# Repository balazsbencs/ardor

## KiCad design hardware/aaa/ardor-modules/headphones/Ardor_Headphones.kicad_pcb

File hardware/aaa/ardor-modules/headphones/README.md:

# Ardor Optional stereo headphones — M1

An external stereo line-level source feeds the local TPA6132A2 and charge pump. No mixer or external negative supply is required.

Power from an external regulated **5 V / 50 mA** supply budget. These figures reserve operating margin; they are not measured consumption. No onboard input regulator or reverse-power protection is provided. Use only the named rails and connect host GND. Budget each fitted module separately.

[Single-page schematic](review/schematic.pdf) · [Component placement](review/pcb-assembly.svg) · [Front routing](review/pcb-front.svg) · [Back routing and connector legends](review/pcb-back.svg)

## Connector pins

All connectors/jumpers are 2.54 mm headers. **Square pad = pin 1.** Pin numbers below are native schematic/PCB numbers, not left-to-right screen positions. Back-side text is read from the back of the physical board. The same reference names appear on multiple modules; use this board’s table. **J101 pin assignments differ between module types; harnesses are not interchangeable.**

| Connector | Pin | Signal |
|---|---|---|
| J102 | 1 | AUDIO_L |
| J102 | 2 | GND |
| J102 | 3 | AUDIO_R |
| J101 | 1 | +5V |
| J101 | 2 | GND |
| J101 | 3 | HP_ENABLE |
| J602 | 1 | HP_L |
| J602 | 2 | HP_R |
| J602 | 3 | GND |

## Wiring and commissioning

Connect an external stereo line-level DAC/codec to J102: pin 1 left, pin 2 ground, pin 3 right; each **≤1 Vrms**. J602 goes to a TRS headphone socket: pin 1 tip/left, pin 2 ring/right, pin 3 sleeve/GND. The sleeve/bushing bonds the enclosure through the local CHASSIS/GND link. Use headphones of **32 Ω or greater**; there is no balanced output.

J101 pin 3 **HP_ENABLE** is a 3.3 V logic input. LOW or disconnected disables the amplifier; HIGH enables it. Keep it low until audio and 5 V are stable, then start at low volume and ramp up. Do not drive enable above the amplifier’s supply plus 0.3 V when unpowered. Both gain pins are grounded, selecting **−6 dB inverting gain**. A 1 Vrms input gives about 0.47 Vrms / 6.8 mW per channel into 32 Ω after the 2.2 Ω output resistors (nominal calculation, not a measured result).

The TPA6132A2 charge-pump flying/storage capacitors, exposed-pad ground and input DC blocking are all local. HPVDD/HPVSS are internal rails and must not be connected to external power. This module deliberately carries the optional QFN amplifier and its added assembly/X-ray cost so other features do not pay for it. The local 0.5 mm pitch QFN land and 0.2 mm drilled thermal vias are frozen in this project; do not substitute a generic footprint in an ordering copy.

Fit J101/J102/J602 by hand. SMT includes U601 and the charge-pump capacitors. Inspect U601 pin 1 and exposed-pad soldering in the JLCPCB preview and delivered boards. Bring-up into resistive dummy loads first: check supplies, enable operation, channel assignment, output DC, charge-pump ripple, clipping/noise and hot-plug behavior. Then test headphones at low volume.

## Order this board

Upload [the fabrication ZIP](assembly/Ardor_Headphones-JLCPCB-Gerbers.zip), [SMT BOM](assembly/jlcpcb-bom.csv) and [CPL](assembly/jlcpcb-cpl.csv) as **one separate design**. Select two assembled boards, two copper layers, 1.6 mm FR-4, 1 oz finished copper, and top-side SMT assembly only. The ZIP includes both silk/mask/copper layers and separate PTH/NPTH drill files. Use the supplied absolute origin throughout; do not apply an auxiliary-origin shift to just the CPL.

The dated parts/loss model is **$9.93** for two boards, plus **$12.28** for 4 Economic Extended feeder types, plus approximately $3.28 QFN X-ray. This excludes PCB/setup/stencil/joints/shipping/tax/manual parts and is not a checkout quote. Public stock was checked **2 October 2026**; no parts are reserved. Recheck the exact C-codes and quantities when ordering.

[Manual-fit BOM](assembly/manual-bom.csv) lists headers. Panel sockets, wires, host, regulated supply, M2 hardware and enclosure are external items, chosen to suit the build; they are not in the SMT order. This PCB has two 2.2 mm NPTH mounting holes. Keep conductive mounting hardware clear of copper.

Inspect **every IC, diode and polarized capacitor** against its pin 1/polarity in JLCPCB’s interactive placement preview. CPL uses native KiCad CCW angles; the supplier may assign a different zero orientation for its part model. That preview has not been checked or approved here. Correct supplier-side rotations before paying.

[Verification summary](verification/validation.json) records clean ERC/DRC/parity, physical pad/net checks, uniform widths and zero inter-module dependencies. These are design checks; the M1 boards have not been built or bench-tested. Complete the commissioning checks above before treating them as validated hardware.

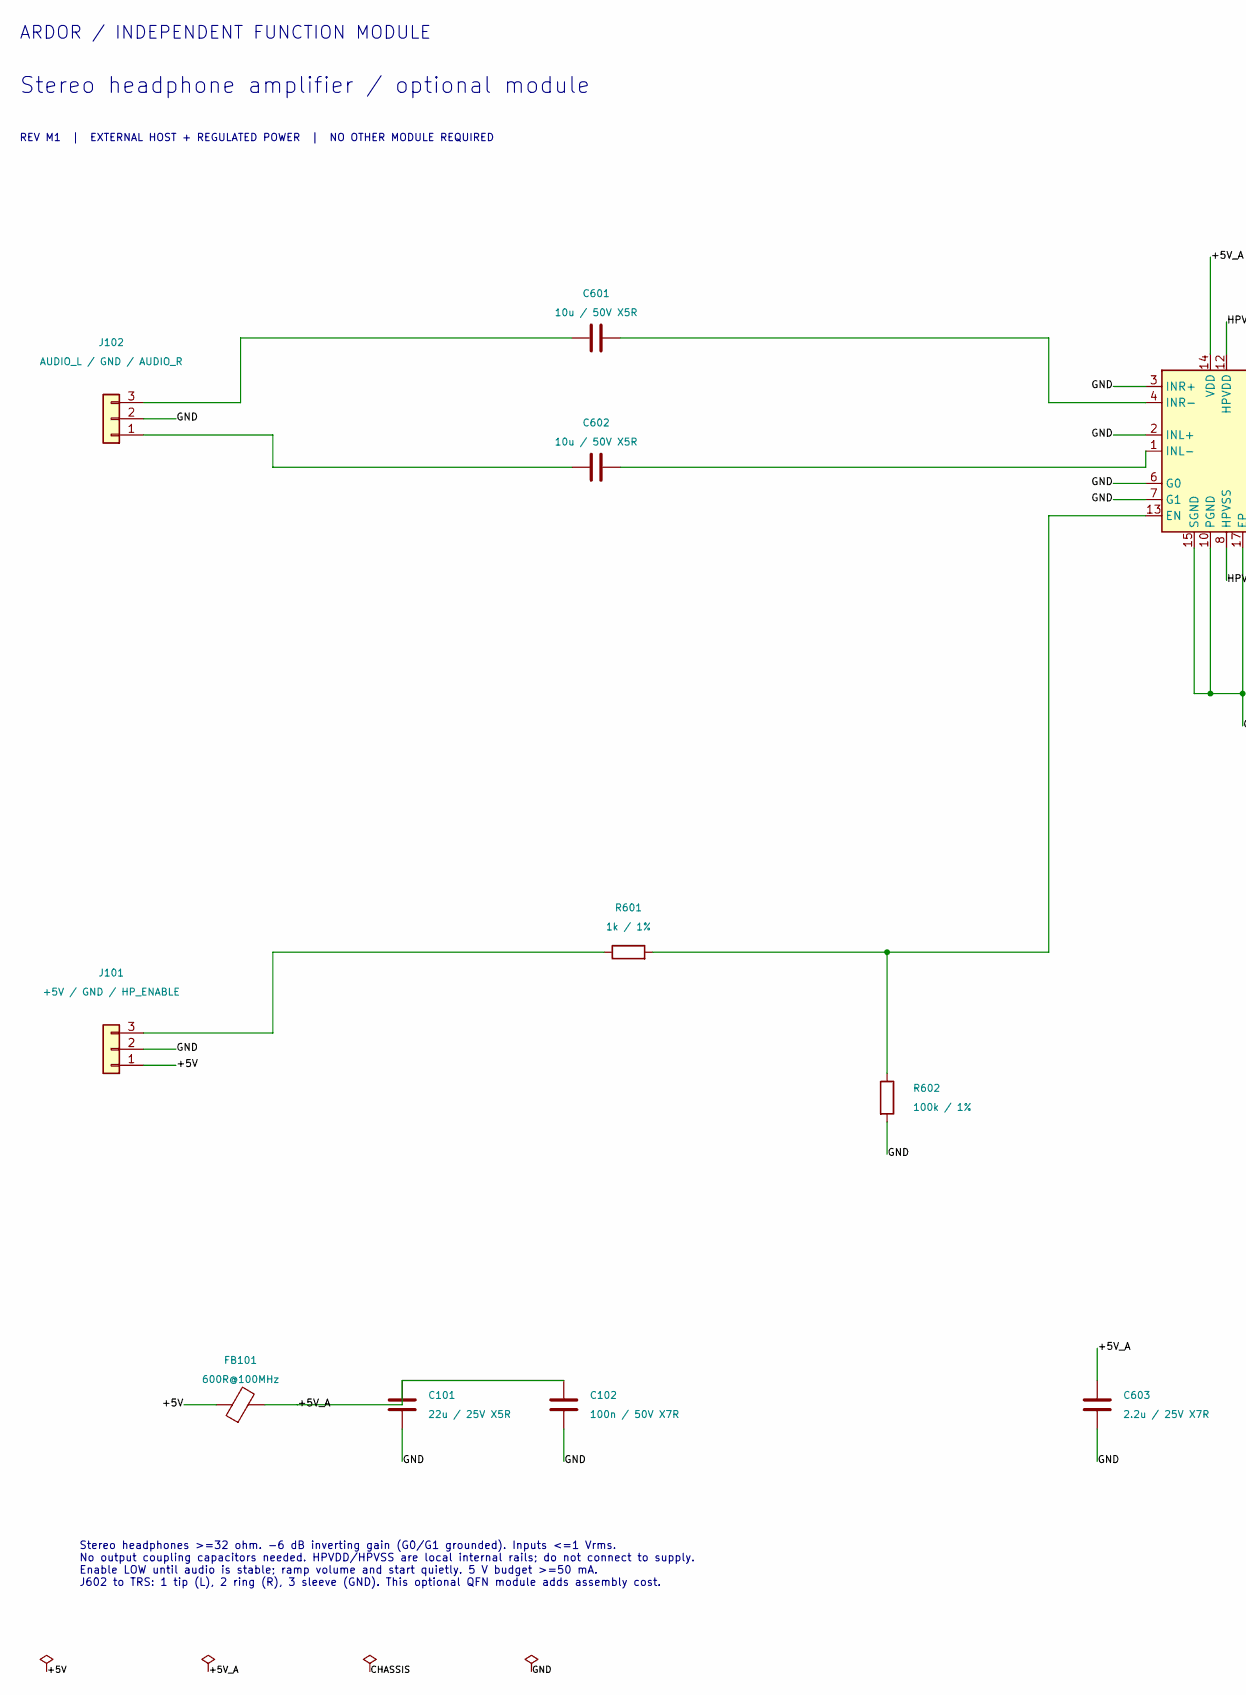
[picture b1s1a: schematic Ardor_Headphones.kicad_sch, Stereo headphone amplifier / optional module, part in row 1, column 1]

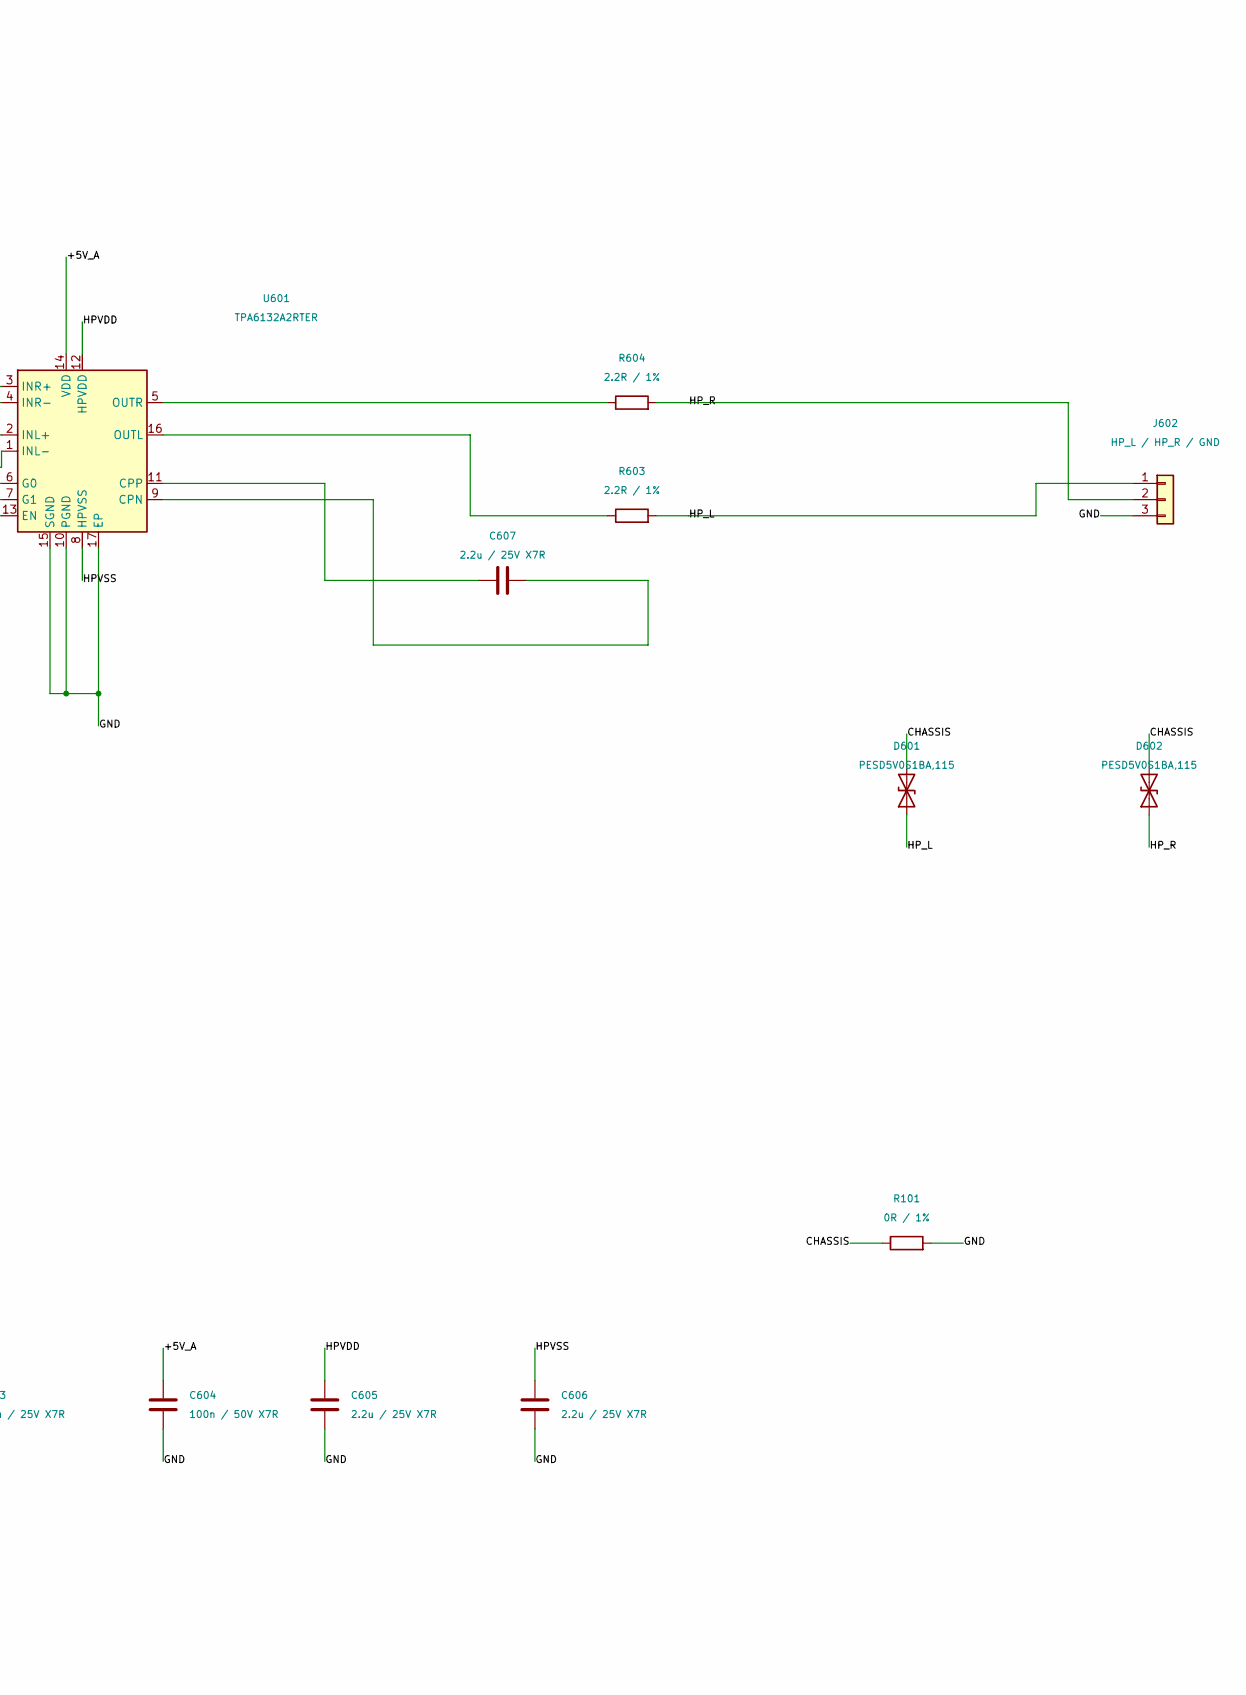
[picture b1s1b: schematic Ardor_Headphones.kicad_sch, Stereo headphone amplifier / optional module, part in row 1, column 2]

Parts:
C101: 22u / 25V X5R; C_0805_2012Metric; MPN Samsung Electro-Mechanics CL21A226MAQNN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; JLCPCB Part # C45783
C102, C604: 100n / 50V X7R; C_0603_1608Metric; MPN YAGEO CC0603KRX7R9BB104; JLCPCB Part # C14663
C601, C602: 10u / 50V X5R; C_1206_3216Metric; MPN Samsung Electro-Mechanics CL31A106KBHNN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; JLCPCB Part # C13585
C603, C605, C606, C607: 2.2u / 25V X7R; C_0805_2012Metric; MPN Samsung CL21B225KAFNNNE; JLCPCB Part # C19110
D601, D602: PESD5V0S1BA,115; D_SOD-323; MPN Nexperia PESD5V0S1BA,115; JLCPCB Part # C19224
FB101: 600R@100MHz; L_0805_2012Metric; MPN Murata BLM21PG601SN1D; JLCPCB Part # C41556732
J101: +5V / GND / HP_ENABLE; PinHeader_1x03_P2.54mm_Vertical; MPN PinHeader_1x03_P2.54mm_Vertical
J102: AUDIO_L / GND / AUDIO_R; PinHeader_1x03_P2.54mm_Vertical; MPN PinHeader_1x03_P2.54mm_Vertical
J602: HP_L / HP_R / GND; PinHeader_1x03_P2.54mm_Vertical; MPN PinHeader_1x03_P2.54mm_Vertical
R101: 0R / 1%; R_1206_3216Metric; MPN UNI-ROYAL 1206W4F0000T5E; JLCPCB Part # C17888
R601: 1k / 1%; R_0603_1608Metric; MPN UNI-ROYAL 0603WAF1001T5E; JLCPCB Part # C21190
R602: 100k / 1%; R_0603_1608Metric; MPN UNI-ROYAL 0603WAF1003T5E; JLCPCB Part # C25803
R603, R604: 2.2R / 1%; R_0603_1608Metric; MPN UNI-ROYAL 0603WAF220KT5E; JLCPCB Part # C22939
U601: TPA6132A2RTER; WQFN-16-1EP_3x3mm_P0.5mm_EP1.6x1.6mm_ThermalVias; MPN TI TPA6132A2RTER; JLCPCB Part # C69901

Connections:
/+5V: FB101.1, J101.1
/+5V_A: C101.1, C102.1, C603.1, C604.1, FB101.2, U601.14 (VDD)
/CHASSIS: D601.2 (A2), D602.2 (A2), R101.1
/GND: C101.2, C102.2, C603.2, C604.2, C605.2, C606.2, J101.2, J102.2, J602.3, R101.2, R602.2, U601.2 (INL+), U601.3 (INR+), U601.6 (G0), U601.7 (G1), U601.10 (PGND), U601.15 (SGND), U601.17 (EP)
/HPVDD: C605.1, U601.12 (HPVDD)
/HPVSS: C606.1, U601.8 (HPVSS)
/HP_L: D601.1 (A1), J602.1, R603.2
/HP_R: D602.1 (A1), J602.2, R604.2
unnamed: J101.3, R601.1
unnamed: C602.1, J102.1
unnamed: C601.1, J102.3
unnamed: C607.2, U601.9 (CPN)
unnamed: C607.1, U601.11 (CPP)
unnamed: R601.2, R602.1, U601.13 (EN)
unnamed: C602.2, U601.1 (INL-)
unnamed: C601.2, U601.4 (INR-)
unnamed: R603.1, U601.16 (OUTL)
unnamed: R604.1, U601.5 (OUTR)

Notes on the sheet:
ARDOR / INDEPENDENT FUNCTION MODULE
Stereo headphone amplifier / optional module
REV M1 | EXTERNAL HOST + REGULATED POWER | NO OTHER MODULE REQUIRED
Stereo headphones >=32 ohm. -6 dB inverting gain (G0/G1 grounded). Inputs <=1 Vrms. No output coupling capacitors needed. HPVDD/HPVSS are local internal rails; do not connect to supply. Enable LOW until audio is stable; ramp volume and start quietly. 5 V budget >=50 mA. J602 to TRS: 1 tip (L), 2 ri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

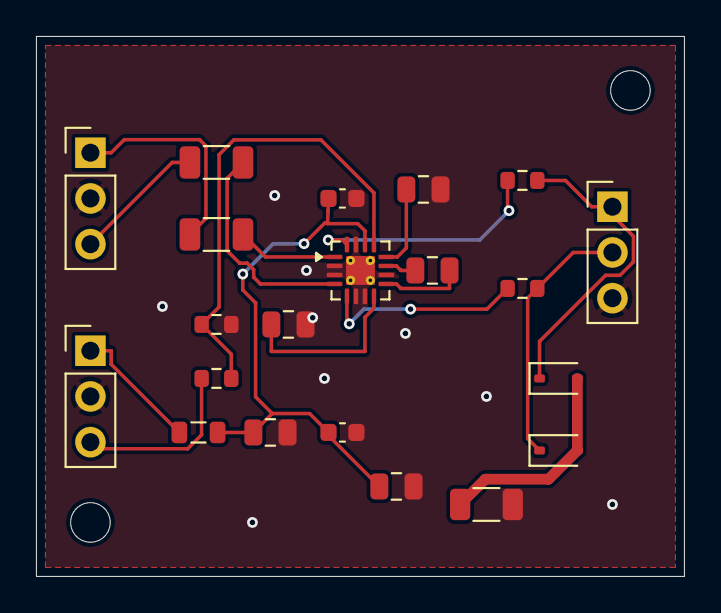
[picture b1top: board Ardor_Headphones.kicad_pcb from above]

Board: 2 copper layers, 36.0 x 30.0 mm, 23 parts (0 on the bottom side), 18 nets.

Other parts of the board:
H1, H2: MountingHole_2.2mm_M2

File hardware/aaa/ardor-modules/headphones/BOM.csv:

Reference,Value,Footprint,MPN,JLCPCB Part #,Assembly
J102,AUDIO_L / GND / AUDIO_R,Connector_PinHeader_2.54mm:PinHeader_1x03_P2.54mm_Vertical,PinHeader_1x03_P2.54mm_Vertical,,Manual
J101,+5V / GND / HP_ENABLE,Connector_PinHeader_2.54mm:PinHeader_1x03_P2.54mm_Vertical,PinHeader_1x03_P2.54mm_Vertical,,Manual
J602,HP_L / HP_R / GND,Connector_PinHeader_2.54mm:PinHeader_1x03_P2.54mm_Vertical,PinHeader_1x03_P2.54mm_Vertical,,Manual
FB101,600R@100MHz,Inductor_SMD:L_0805_2012Metric,Murata BLM21PG601SN1D,C41556732,SMT
C101,22u / 25V X5R,Capacitor_SMD:C_0805_2012Metric,Samsung Electro-Mechanics CL21A226MAQNNNE,C45783,SMT
C102,100n / 50V X7R,Capacitor_SMD:C_0603_1608Metric,YAGEO CC0603KRX7R9BB104,C14663,SMT
C601,10u / 50V X5R,Capacitor_SMD:C_1206_3216Metric,Samsung Electro-Mechanics CL31A106KBHNNNE,C13585,SMT
C602,10u / 50V X5R,Capacitor_SMD:C_1206_3216Metric,Samsung Electro-Mechanics CL31A106KBHNNNE,C13585,SMT
U601,TPA6132A2RTER,Package_DFN_QFN:WQFN-16-1EP_3x3mm_P0.5mm_EP1.6x1.6mm_ThermalVias,TI TPA6132A2RTER,C69901,SMT
R601,1k / 1%,Resistor_SMD:R_0603_1608Metric,UNI-ROYAL 0603WAF1001T5E,C21190,SMT
R602,100k / 1%,Resistor_SMD:R_0603_1608Metric,UNI-ROYAL 0603WAF1003T5E,C25803,SMT
R603,2.2R / 1%,Resistor_SMD:R_0603_1608Metric,UNI-ROYAL 0603WAF220KT5E,C22939,SMT
R604,2.2R / 1%,Resistor_SMD:R_0603_1608Metric,UNI-ROYAL 0603WAF220KT5E,C22939,SMT
D601,"PESD5V0S1BA,115",Diode_SMD:D_SOD-323,"Nexperia PESD5V0S1BA,115",C19224,SMT
D602,"PESD5V0S1BA,115",Diode_SMD:D_SOD-323,"Nexperia PESD5V0S1BA,115",C19224,SMT
R101,0R / 1%,Resistor_SMD:R_1206_3216Metric,UNI-ROYAL 1206W4F0000T5E,C17888,SMT
C603,2.2u / 25V X7R,Capacitor_SMD:C_0805_2012Metric,Samsung CL21B225KAFNNNE,C19110,SMT
C604,100n / 50V X7R,Capacitor_SMD:C_0603_1608Metric,YAGEO CC0603KRX7R9BB104,C14663,SMT
C605,2.2u / 25V X7R,Capacitor_SMD:C_0805_2012Metric,Samsung CL21B225KAFNNNE,C19110,SMT
C606,2.2u / 25V X7R,Capacitor_SMD:C_0805_2012Metric,Samsung CL21B225KAFNNNE,C19110,SMT
C607,2.2u / 25V X7R,Capacitor_SMD:C_0805_2012Metric,Samsung CL21B225KAFNNNE,C19110,SMT

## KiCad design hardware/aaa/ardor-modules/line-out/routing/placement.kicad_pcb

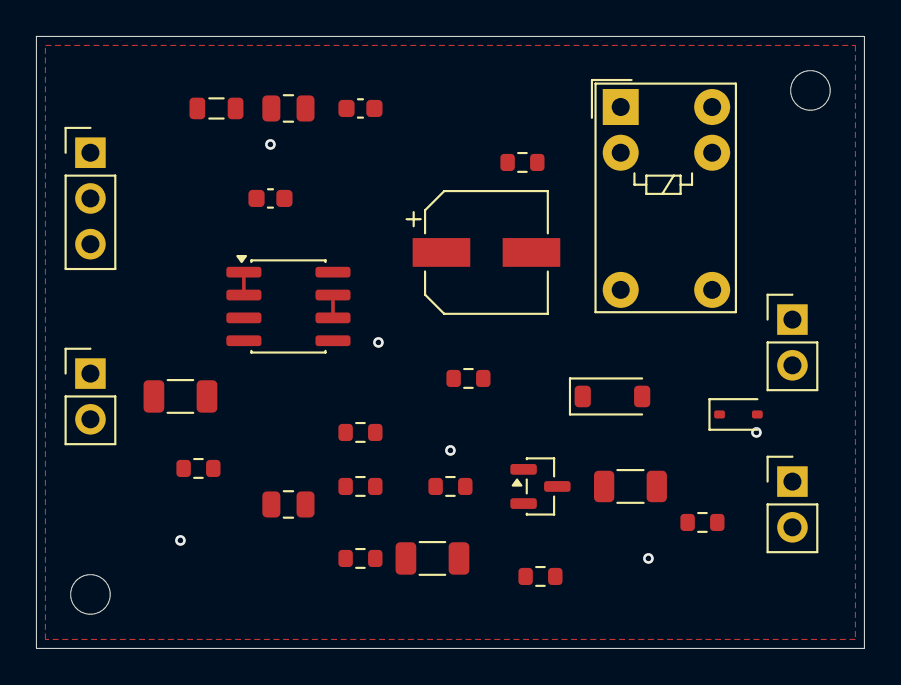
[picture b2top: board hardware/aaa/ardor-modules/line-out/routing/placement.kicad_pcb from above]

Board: 2 copper layers, 46.0 x 34.0 mm, 29 parts (0 on the bottom side), 17 nets.

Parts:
C101: 22u / 25V X5R; C_0805_2012Metric
C102, C404: 100n / 50V X7R; C_0603_1608Metric
C401, C502: 10u / 50V X5R; C_1206_3216Metric
C403: 10u / 25V X5R; C_0805_2012Metric
C501: EEEFK1C470P; CP_Elec_Panasonic_FK_D6.3_H5.8
D501: PESD5V0S1BA,115; D_SOD-323
D502: 1N4148W; D_SOD-123
FB101: BLM21PG601SN1D; L_0805_2012Metric
H1, H2: MountingHole_2.2mm_M2
J101: +5V / GND / LINE_ENABLE; PinHeader_1x03_P2.54mm_Vertical
J102: AUDIO_IN / GND; PinHeader_1x02_P2.54mm_Vertical
J502: AMP_FEED / GND; PinHeader_1x02_P2.54mm_Vertical
J503: LINE_JACK / GND; PinHeader_1x02_P2.54mm_Vertical
K501: Omron G5V-1 DC5; Relay_SPDT_Omron_G5V-1
Q501: AO3400A; SOT-23
R101: 0R / 1%; R_1206_3216Metric
R401, R504, R506: 100kR / 1%; R_0603_1608Metric
R405, R406, R501: 10kR / 1%; R_0603_1608Metric
R502: 100R / 1%; R_0603_1608Metric
R503, R505: 1kR / 1%; R_0603_1608Metric
U501: TLV9002IDR; SOIC-8_3.9x4.9mm_P1.27mm

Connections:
/+5V: D502.1, FB101.1, J101.1, K501.2
/+5V_A: C101.1, C102.1, C404.1, FB101.2, R405.1, U501.8
/CHASSIS: D501.2, R101.1
/GND: C101.2, C102.2, C403.2, C404.2, J101.2, J102.2, J502.2, J503.2, K501.1, Q501.2, R101.2, R406.2, R501.2, R504.2, R506.2, U501.4
/VREF: R401.2, U501.6, U501.7
unnamed: C501.2, R501.1, R502.1
unnamed: C502.2, R505.1
unnamed: D501.1, J503.1, K501.5, K501.6
unnamed: D502.2, K501.9, Q501.3
unnamed: J101.3, R503.1
unnamed: C401.1, J102.1
unnamed: J502.1, R505.2, R506.1
unnamed: K501.10, R502.2
unnamed: Q501.1, R503.2, R504.1
unnamed: C401.2, R401.1, U501.3
unnamed: C501.1, C502.1, U501.1, U501.2
unnamed: C403.1, R405.2, R406.1, U501.5

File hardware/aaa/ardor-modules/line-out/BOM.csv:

Reference,Value,Footprint,MPN,JLCPCB Part #,Assembly
J102,AUDIO_IN / GND,Connector_PinHeader_2.54mm:PinHeader_1x02_P2.54mm_Vertical,PinHeader_1x02_P2.54mm_Vertical,,Manual
J101,+5V / GND / LINE_ENABLE,Connector_PinHeader_2.54mm:PinHeader_1x03_P2.54mm_Vertical,PinHeader_1x03_P2.54mm_Vertical,,Manual
J503,LINE_JACK / GND,Connector_PinHeader_2.54mm:PinHeader_1x02_P2.54mm_Vertical,PinHeader_1x02_P2.54mm_Vertical,,Manual
J502,AMP_FEED / GND,Connector_PinHeader_2.54mm:PinHeader_1x02_P2.54mm_Vertical,PinHeader_1x02_P2.54mm_Vertical,,Manual
FB101,600R@100MHz,Inductor_SMD:L_0805_2012Metric,Murata BLM21PG601SN1D,C41556732,SMT
C101,22u / 25V X5R,Capacitor_SMD:C_0805_2012Metric,Samsung Electro-Mechanics CL21A226MAQNNNE,C45783,SMT
C102,100n / 50V X7R,Capacitor_SMD:C_0603_1608Metric,YAGEO CC0603KRX7R9BB104,C14663,SMT
C401,10u / 50V X5R,Capacitor_SMD:C_1206_3216Metric,Samsung Electro-Mechanics CL31A106KBHNNNE,C13585,SMT
R401,100k / 1%,Resistor_SMD:R_0603_1608Metric,UNI-ROYAL 0603WAF1003T5E,C25803,SMT
U501,TLV9002IDR,Package_SO:SOIC-8_3.9x4.9mm_P1.27mm,Texas Instruments TLV9002IDR,C398360,SMT
C501,47u / 16V polarized,Ardor_Capacitor:CP_Elec_Panasonic_FK_D6.3_H5.8,Panasonic EEEFK1C470P,C336261,SMT
R501,10k / 1%,Resistor_SMD:R_0603_1608Metric,UNI-ROYAL 0603WAF1002T5E,C25804,SMT
R502,100R / 1%,Resistor_SMD:R_0603_1608Metric,UNI-ROYAL 0603WAF1000T5E,C22775,SMT
K501,Omron G5V-1 DC5,Relay_THT:Relay_SPDT_Omron_G5V-1,Omron G5V-1 DC5,,Manual
D501,"PESD5V0S1BA,115",Diode_SMD:D_SOD-323,"Nexperia PESD5V0S1BA,115",C19224,SMT
R101,0R / 1%,Resistor_SMD:R_1206_3216Metric,UNI-ROYAL 1206W4F0000T5E,C17888,SMT
Q501,AO3400A,Package_TO_SOT_SMD:SOT-23,Alpha & Omega AO3400A,C20917,SMT
R503,1k / 1%,Resistor_SMD:R_0603_1608Metric,UNI-ROYAL 0603WAF1001T5E,C21190,SMT
R504,100k / 1%,Resistor_SMD:R_0603_1608Metric,UNI-ROYAL 0603WAF1003T5E,C25803,SMT
D502,1N4148W,Diode_SMD:D_SOD-123,ST(Semtech) 1N4148W,C81598,SMT
R405,10k / 1%,Resistor_SMD:R_0603_1608Metric,UNI-ROYAL 0603WAF1002T5E,C25804,SMT
R406,10k / 1%,Resistor_SMD:R_0603_1608Metric,UNI-ROYAL 0603WAF1002T5E,C25804,SMT
C403,10u / 25V X5R,Capacitor_SMD:C_0805_2012Metric,Samsung Electro-Mechanics CL21A106KAYNNNE,C15850,SMT
C404,100n / 50V X7R,Capacitor_SMD:C_0603_1608Metric,YAGEO CC0603KRX7R9BB104,C14663,SMT
C502,10u / 50V X5R,Capacitor_SMD:C_1206_3216Metric,Samsung Electro-Mechanics CL31A106KBHNNNE,C13585,SMT
R505,1k / 1%,Resistor_SMD:R_0603_1608Metric,UNI-ROYAL 0603WAF1001T5E,C21190,SMT
R506,100k / 1%,Resistor_SMD:R_0603_1608Metric,UNI-ROYAL 0603WAF1003T5E,C25803,SMT

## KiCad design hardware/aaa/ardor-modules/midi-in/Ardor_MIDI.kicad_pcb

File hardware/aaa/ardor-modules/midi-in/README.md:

# Ardor DIN MIDI input — M1

Isolated current-loop input to a 3.3 V UART. No expression board, mixer, codec, carrier or shared bias circuit is required.

Power from an external regulated **5 V / 10 mA and 3.3 V / 5 mA** supply budget. These figures reserve operating margin; they are not measured consumption. No onboard input regulator or reverse-power protection is provided. Use only the named rails and connect host GND. Budget each fitted module separately.

[Single-page schematic](review/schematic.pdf) · [Component placement](review/pcb-assembly.svg) · [Front routing](review/pcb-front.svg) · [Back routing and connector legends](review/pcb-back.svg)

[Short assembly guide](ASSEMBLY.md) · [Beginner pin card](review/wiring-guide.pdf)

## Connector pins

All connectors/jumpers are 2.54 mm headers. **Square pad = pin 1.** Pin numbers below are native schematic/PCB numbers, not left-to-right screen positions. Back-side text is read from the back of the physical board. The same reference names appear on multiple modules; use this board’s table. **J101 pin assignments differ between module types; harnesses are not interchangeable.**

| Connector | Pin | Direction / function | Connect to |
|---|---|---|---|
| J202 | 1 | **MIDI INPUT** — MIDI current-loop input, DIN contact 4. | Female DIN socket numbered contact 4. |
| J202 | 2 | **MIDI INPUT** — MIDI current-loop return, DIN contact 5; NOT GND. | Female DIN socket numbered contact 5. |
| J101 | 1 | **POWER INPUT** — Feed regulated 5V into the module. This pin does not supply power. | Positive output of the matching regulated supply. |
| J101 | 2 | **POWER INPUT** — Feed regulated 3V3 into the module. This pin does not supply power. | Positive output of the matching regulated supply. |
| J101 | 3 | **GROUND** — Common 0 V return; not a signal or positive supply. | Host or cable ground / 0 V. |
| J101 | 4 | **OUTPUT** — 3.3 V decoded MIDI logic leaves the module; this is not a DIN MIDI output. | Host UART RX input, 31250 baud, 8-N-1. Do not connect to host TX. |
| J203 | 1 | **BOND** — Enclosure/chassis connection, locally joined to GND through R101. | Aluminium enclosure bonding point; insulate the MIDI DIN shell. |
| J203 | 2 | **GROUND** — Common 0 V return; not a signal or positive supply. | Host or cable ground / 0 V. |

**IN** enters this board. **OUT** leaves this board. **I/O** uses both directions. **GND** is the common 0 V return. **3V3** means 3.3 V.

Unused component pins: **U201.3** — NC - LEAVE OPEN. The factory/hand solder joint remains; do not add an external wire.

H1/H2 are mounting holes. Small via holes and other component pads are not wire connectors.

## Wiring and commissioning

Connect J202 pin 1 to contact **4** and pin 2 to contact **5** of a female 5-pin DIN socket. Use the socket manufacturer’s numbered terminals; the solder-side view is mirrored relative to the mating view. Leave contacts 1, 2, 3 and the socket shell unconnected, and insulate the MIDI socket shell from the enclosure. This preserves the MIDI input current-loop isolation.

J101 pin 4 is **MIDI_RX**, a 3.3 V logic output: UART RX, 31,250 baud, 8 data bits, no parity, one stop bit. It is not a MIDI output or USB interface. J101 needs both regulated supply rails; the 5 V rail powers the H11L1M and the 3.3 V rail sets the UART output high level.

For a metal enclosure, bond J203 pin 1 (CHASSIS) directly to the enclosure. R101 already joins CHASSIS to local GND; J203 pin 2 provides a GND terminal, not an isolated ground. This bond does not require an audio-jack module. In a plastic enclosure retain the local CHASSIS/GND network and omit the enclosure wire. The input-side keepout excludes both GND pours; the native rule requires 3 mm between current-loop and logic copper except the intentional ESD/RF network. This is functional MIDI ground-loop isolation, not certified safety isolation.

Fit U201 **onsemi H11L1M**, DIP-6, by hand, observing pin 1/notch. H11L1M is not interchangeable with a bare phototransistor optocoupler. Fit J101/J202/J203 headers or solder cables to the numbered pads. The receiver includes reverse LED protection, differential TVS, common-mode chassis TVS and RF capacitors.

Bring-up: verify 5 V and 3.3 V first. With no MIDI source, RX should be high. Connect a known MIDI transmitter and confirm correctly decoded messages without parity/framing errors. Verify no DC connection from DIN contacts 4/5 to logic ground when the protection devices are not conducting.

## Order this board

Upload [the fabrication ZIP](assembly/Ardor_MIDI-JLCPCB-Gerbers.zip), [SMT BOM](assembly/jlcpcb-bom.csv) and [CPL](assembly/jlcpcb-cpl.csv) as **one separate design**. Select two assembled boards, two copper layers, 1.6 mm FR-4, 1 oz finished copper, and top-side SMT assembly only. The ZIP includes both silk/mask/copper layers and separate PTH/NPTH drill files. Use the supplied absolute origin throughout; do not apply an auxiliary-origin shift to just the CPL.

The dated parts/loss model is **$5.22** for two boards, plus **$9.21** for 3 Economic Extended feeder types. This excludes PCB/setup/stencil/joints/shipping/tax/manual parts and is not a checkout quote. Public stock was checked **2 October 2026**; no parts are reserved. Recheck the exact C-codes and quantities when ordering.

[Manual-fit BOM](assembly/manual-bom.csv) lists headers, optocoupler. Panel sockets, wires, host, regulated supply, M2 hardware and enclosure are external items, chosen to suit the build; they are not in the SMT order. This PCB has two 2.2 mm NPTH mounting holes. Keep conductive mounting hardware clear of copper.

Inspect **every IC, diode and polarized capacitor** against its pin 1/polarity in JLCPCB’s interactive placement preview. CPL uses native KiCad CCW angles; the supplier may assign a different zero orientation for its part model. That preview has not been checked or approved here. Correct supplier-side rotations before paying.

[Verification summary](verification/validation.json) records clean ERC/DRC/parity, physical pad/net checks, uniform widths and zero inter-module dependencies. These are design checks; the M1 boards have not been built or bench-tested. Complete the commissioning checks above before treating them as validated hardware.

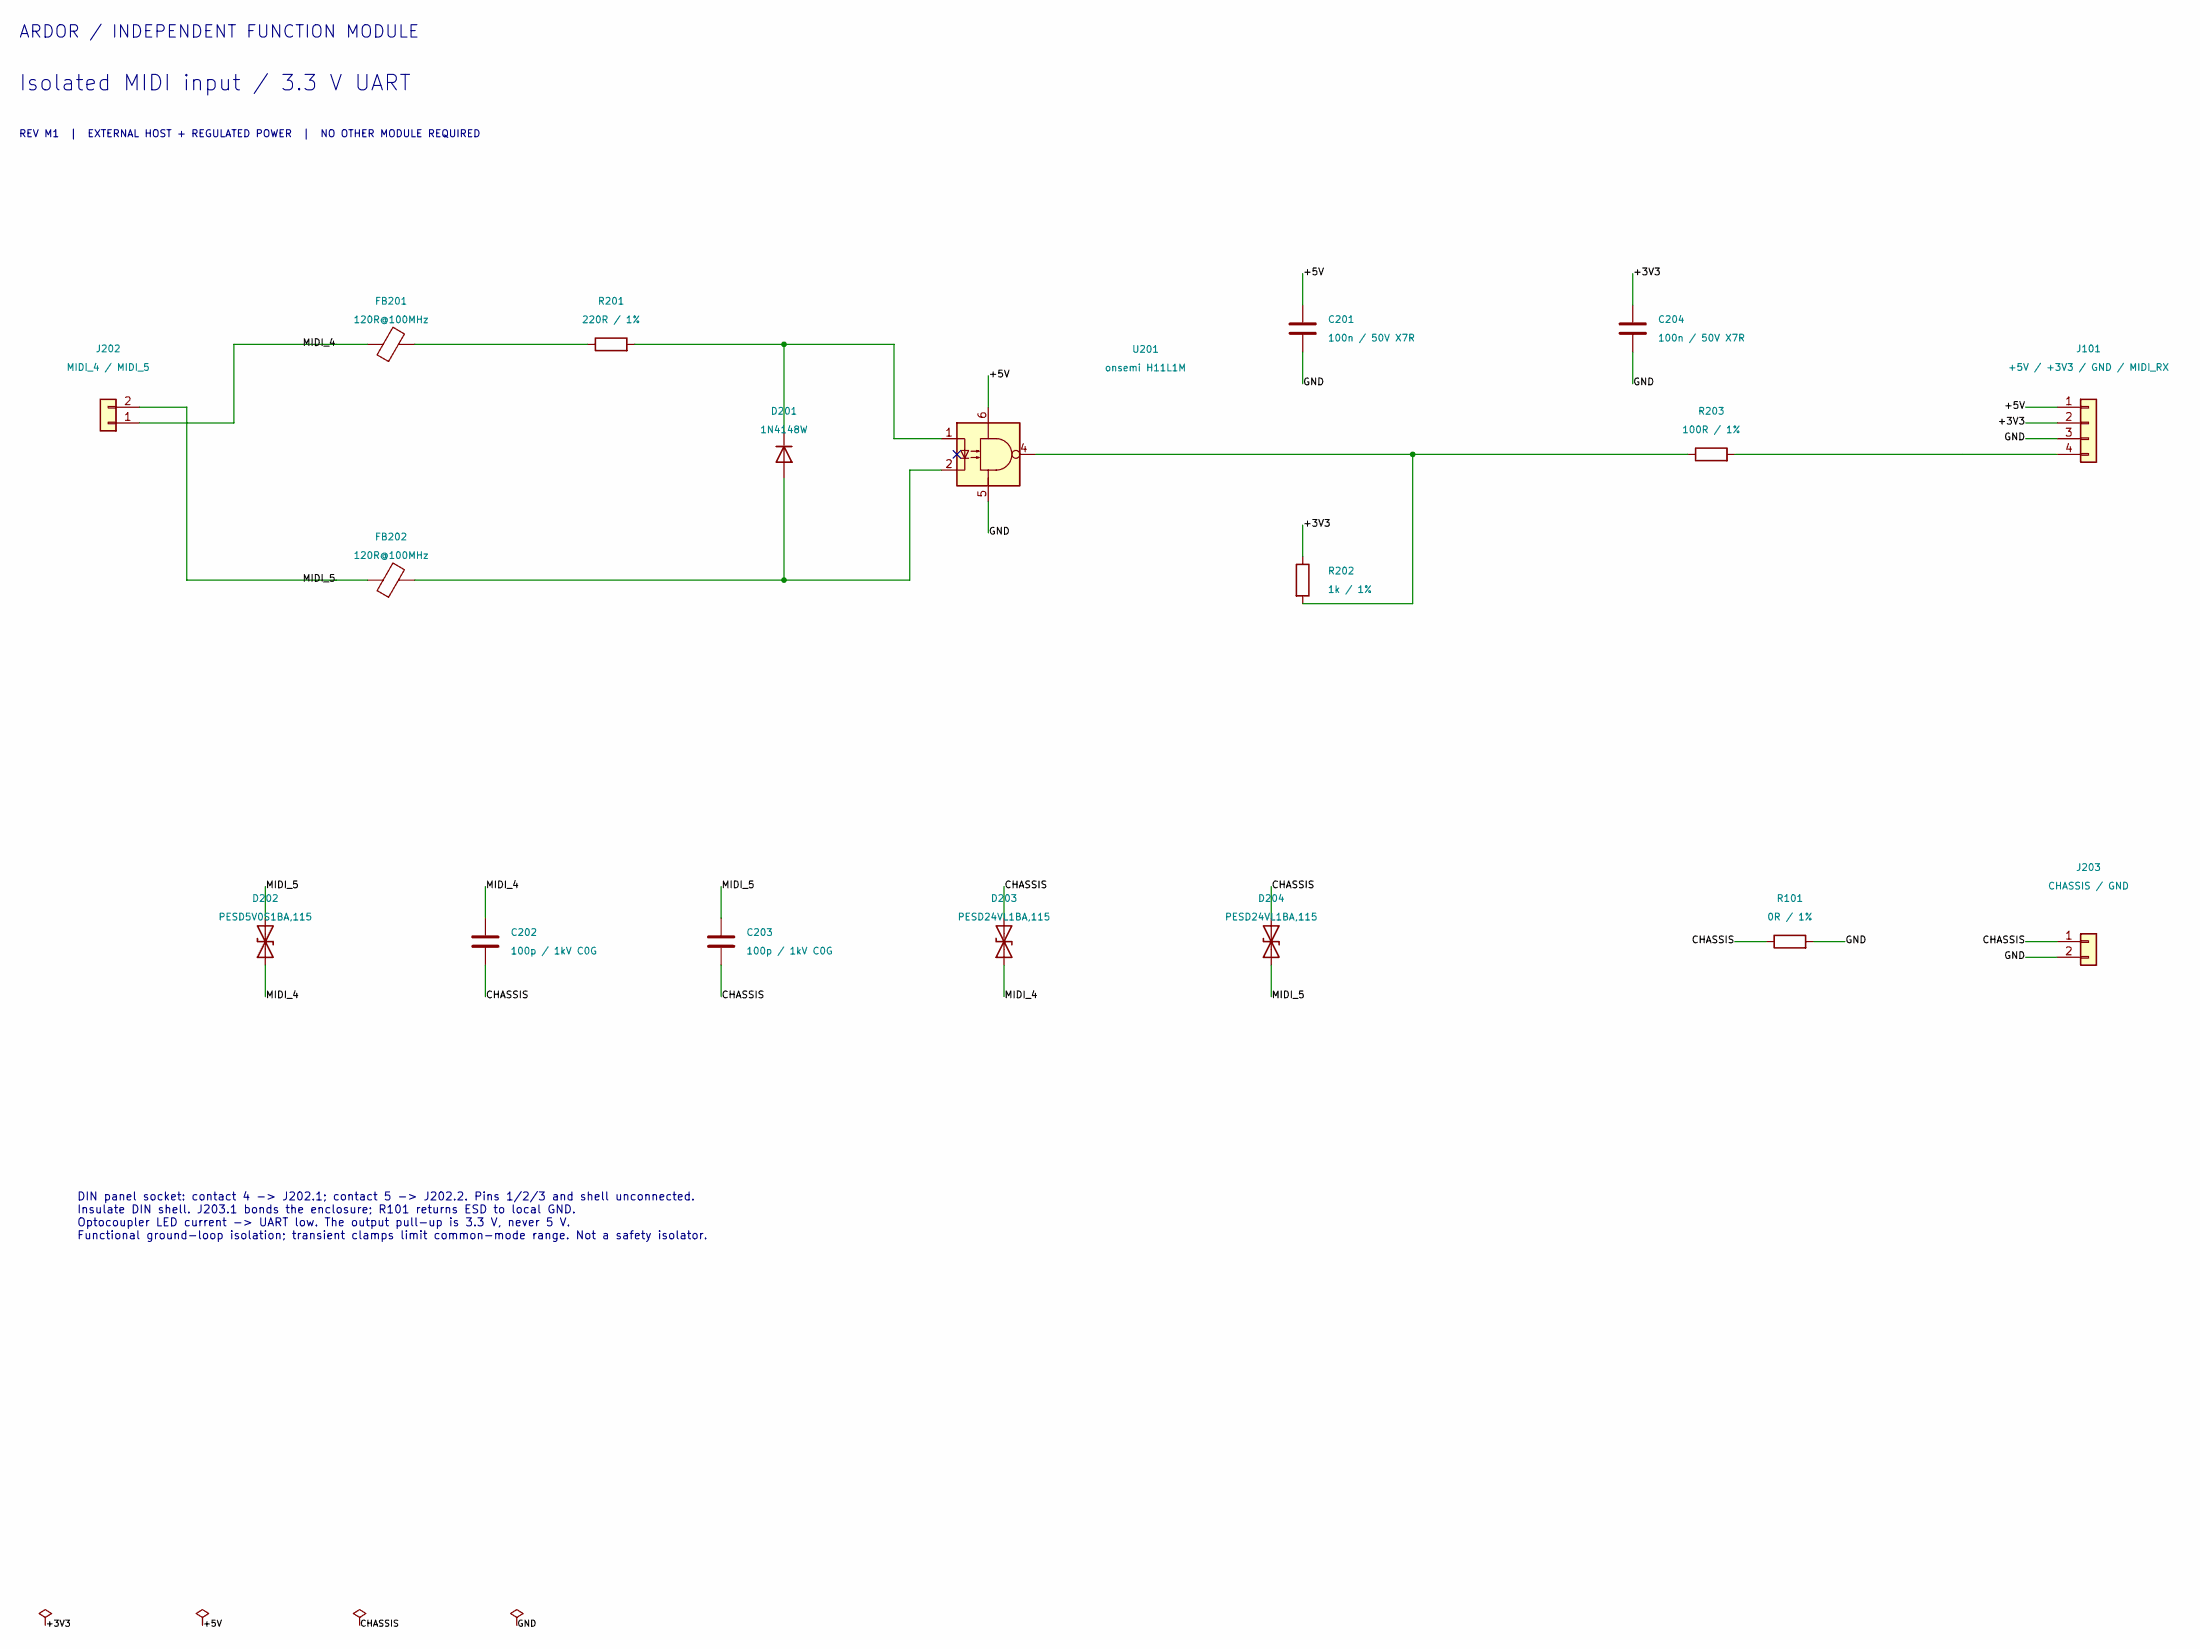
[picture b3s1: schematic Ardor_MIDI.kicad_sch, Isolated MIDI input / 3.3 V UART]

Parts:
C201, C204: 100n / 50V X7R; C_0603_1608Metric; MPN YAGEO CC0603KRX7R9BB104; JLCPCB Part # C14663
C202, C203: 100p / 1kV C0G; C_1206_3216Metric; MPN CCTC TCC1206COG101J102DT; JLCPCB Part # C367316
D201: 1N4148W; D_SOD-123; MPN ST(Semtech) 1N4148W; JLCPCB Part # C81598
D202: PESD5V0S1BA,115; D_SOD-323; MPN Nexperia PESD5V0S1BA,115; JLCPCB Part # C19224
D203, D204: PESD24VL1BA,115; D_SOD-323; MPN Nexperia PESD24VL1BA,115; JLCPCB Part # C69324
FB201, FB202: 120R@100MHz; R_0603_1608Metric; MPN Murata Electronics BLM18PG121SN1D; JLCPCB Part # C14709
J101: +5V / +3V3 / GND / MIDI_RX; PinHeader_1x04_P2.54mm_Vertical; MPN PinHeader_1x04_P2.54mm_Vertical
J202: MIDI_4 / MIDI_5; PinHeader_1x02_P2.54mm_Vertical; MPN PinHeader_1x02_P2.54mm_Vertical
J203: CHASSIS / GND; PinHeader_1x02_P2.54mm_Vertical; MPN PinHeader_1x02_P2.54mm_Vertical
R101: 0R / 1%; R_1206_3216Metric; MPN UNI-ROYAL 1206W4F0000T5E; JLCPCB Part # C17888
R201: 220R / 1%; R_0603_1608Metric; MPN UNI-ROYAL 0603WAF2200T5E; JLCPCB Part # C22962
R202: 1k / 1%; R_0603_1608Metric; MPN UNI-ROYAL 0603WAF1001T5E; JLCPCB Part # C21190
R203: 100R / 1%; R_0603_1608Metric; MPN UNI-ROYAL 0603WAF1000T5E; JLCPCB Part # C22775
U201: onsemi H11L1M; DIP-6_W7.62mm; MPN onsemi H11L1M

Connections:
/+3V3: C204.1, J101.2, R202.1
/+5V: C201.1, J101.1, U201.6
/CHASSIS: C202.2, C203.2, D203.2 (A2), D204.2 (A2), J203.1, R101.1
/GND: C201.2, C204.2, J101.3, J203.2, R101.2, U201.5
/MIDI_4: C202.1, D202.1 (A1), D203.1 (A1), FB201.1, J202.1
/MIDI_5: C203.1, D202.2 (A2), D204.1 (A1), FB202.1, J202.2
unnamed: D201.2 (A), FB202.2, U201.2
unnamed: D201.1 (K), R201.2, U201.1
unnamed: FB201.2, R201.1
unnamed: J101.4, R203.2
unnamed: R202.2, R203.1, U201.4

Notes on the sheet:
ARDOR / INDEPENDENT FUNCTION MODULE
Isolated MIDI input / 3.3 V UART
REV M1 | EXTERNAL HOST + REGULATED POWER | NO OTHER MODULE REQUIRED
DIN panel socket: contact 4 -> J202.1; contact 5 -> J202.2. Pins 1/2/3 and shell unconnected. Insulate DIN shell. J203.1 bonds the enclosure; R101 returns ESD to local GND. Optocoupler LED current -> UART low. The output pull-up is 3.3 V, never 5 V. Functional ground-loop isolation; transient clamp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

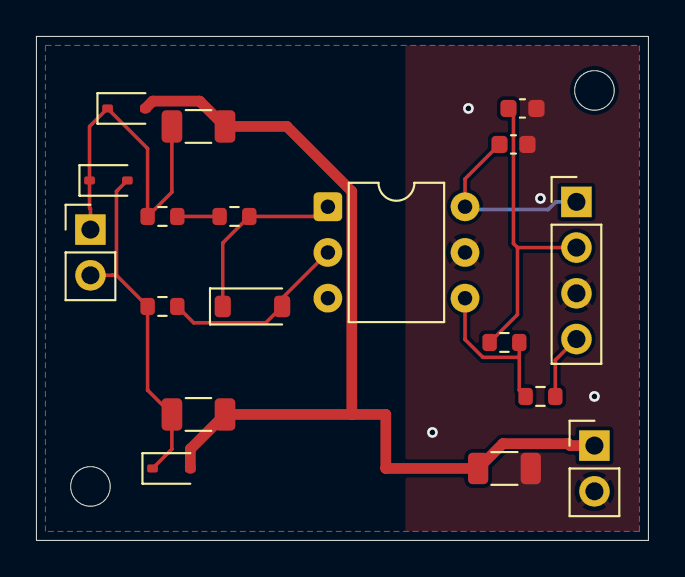
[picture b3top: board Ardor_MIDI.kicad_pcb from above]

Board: 2 copper layers, 34.0 x 28.0 mm, 20 parts (0 on the bottom side), 11 nets.

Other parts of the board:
H1, H2: MountingHole_2.2mm_M2

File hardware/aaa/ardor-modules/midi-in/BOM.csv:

Reference,Value,Footprint,MPN,JLCPCB Part #,Assembly
J202,MIDI_4 / MIDI_5,Connector_PinHeader_2.54mm:PinHeader_1x02_P2.54mm_Vertical,PinHeader_1x02_P2.54mm_Vertical,,Manual
J101,+5V / +3V3 / GND / MIDI_RX,Connector_PinHeader_2.54mm:PinHeader_1x04_P2.54mm_Vertical,PinHeader_1x04_P2.54mm_Vertical,,Manual
J203,CHASSIS / GND,Connector_PinHeader_2.54mm:PinHeader_1x02_P2.54mm_Vertical,PinHeader_1x02_P2.54mm_Vertical,,Manual
FB201,120R@100MHz,Resistor_SMD:R_0603_1608Metric,Murata Electronics BLM18PG121SN1D,C14709,SMT
R201,220R / 1%,Resistor_SMD:R_0603_1608Metric,UNI-ROYAL 0603WAF2200T5E,C22962,SMT
FB202,120R@100MHz,Resistor_SMD:R_0603_1608Metric,Murata Electronics BLM18PG121SN1D,C14709,SMT
U201,onsemi H11L1M,Package_DIP:DIP-6_W7.62mm,onsemi H11L1M,,Manual
D201,1N4148W,Diode_SMD:D_SOD-123,ST(Semtech) 1N4148W,C81598,SMT
C201,100n / 50V X7R,Capacitor_SMD:C_0603_1608Metric,YAGEO CC0603KRX7R9BB104,C14663,SMT
C204,100n / 50V X7R,Capacitor_SMD:C_0603_1608Metric,YAGEO CC0603KRX7R9BB104,C14663,SMT
R202,1k / 1%,Resistor_SMD:R_0603_1608Metric,UNI-ROYAL 0603WAF1001T5E,C21190,SMT
R203,100R / 1%,Resistor_SMD:R_0603_1608Metric,UNI-ROYAL 0603WAF1000T5E,C22775,SMT
D202,"PESD5V0S1BA,115",Diode_SMD:D_SOD-323,"Nexperia PESD5V0S1BA,115",C19224,SMT
C202,100p / 1kV C0G,Capacitor_SMD:C_1206_3216Metric,CCTC TCC1206COG101J102DT,C367316,SMT
C203,100p / 1kV C0G,Capacitor_SMD:C_1206_3216Metric,CCTC TCC1206COG101J102DT,C367316,SMT
D203,"PESD24VL1BA,115",Diode_SMD:D_SOD-323,"Nexperia PESD24VL1BA,115",C69324,SMT
D204,"PESD24VL1BA,115",Diode_SMD:D_SOD-323,"Nexperia PESD24VL1BA,115",C69324,SMT
R101,0R / 1%,Resistor_SMD:R_1206_3216Metric,UNI-ROYAL 1206W4F0000T5E,C17888,SMT
